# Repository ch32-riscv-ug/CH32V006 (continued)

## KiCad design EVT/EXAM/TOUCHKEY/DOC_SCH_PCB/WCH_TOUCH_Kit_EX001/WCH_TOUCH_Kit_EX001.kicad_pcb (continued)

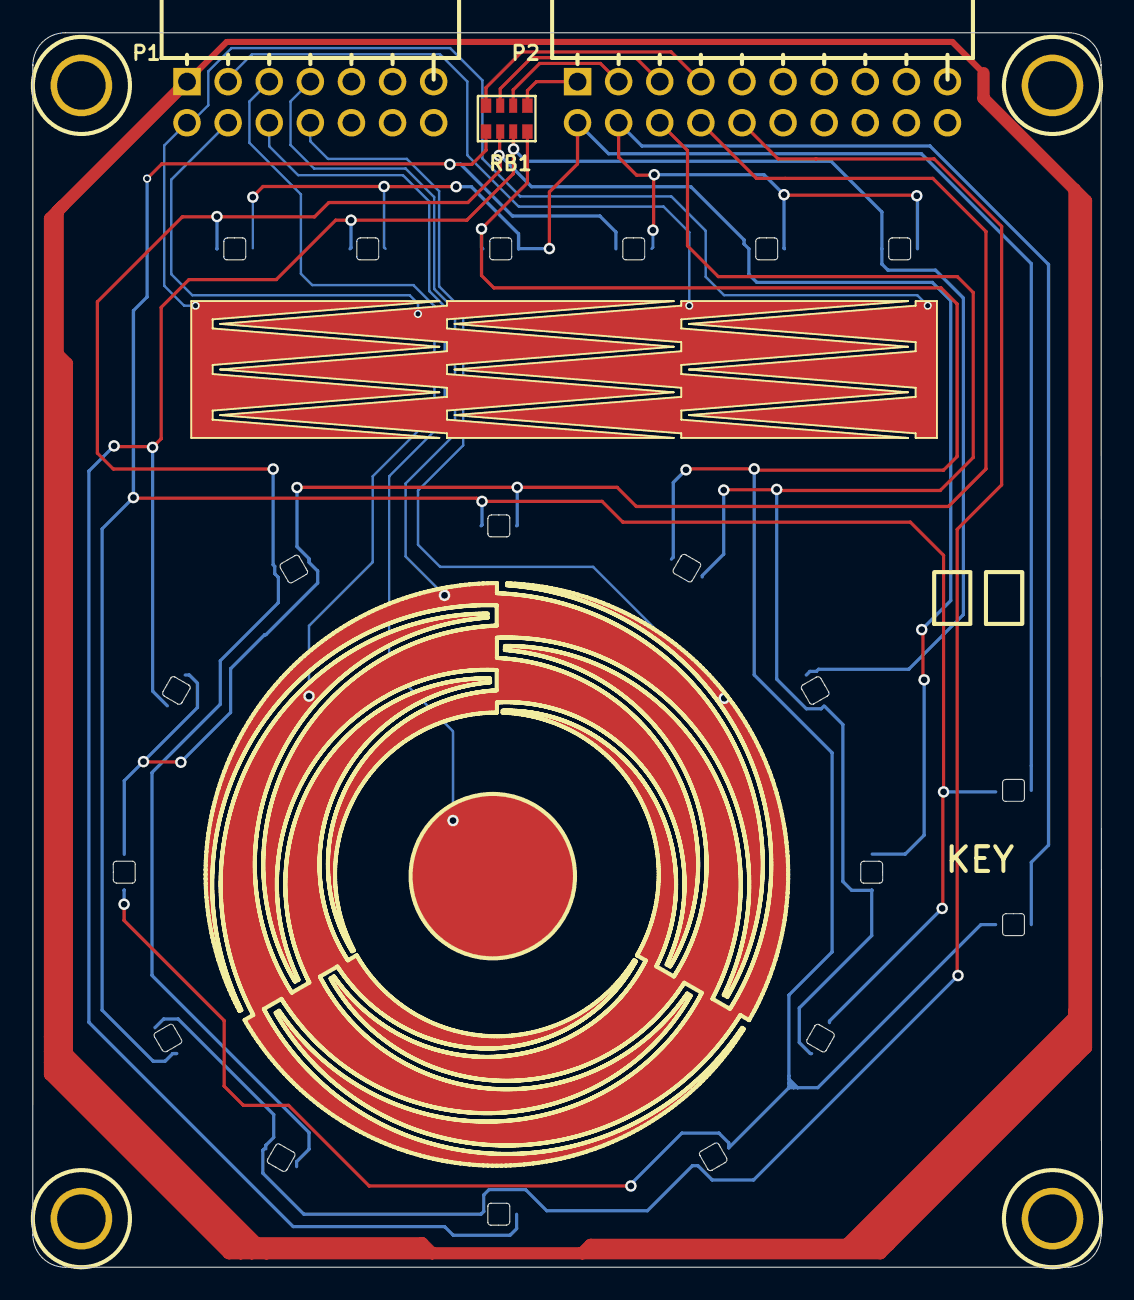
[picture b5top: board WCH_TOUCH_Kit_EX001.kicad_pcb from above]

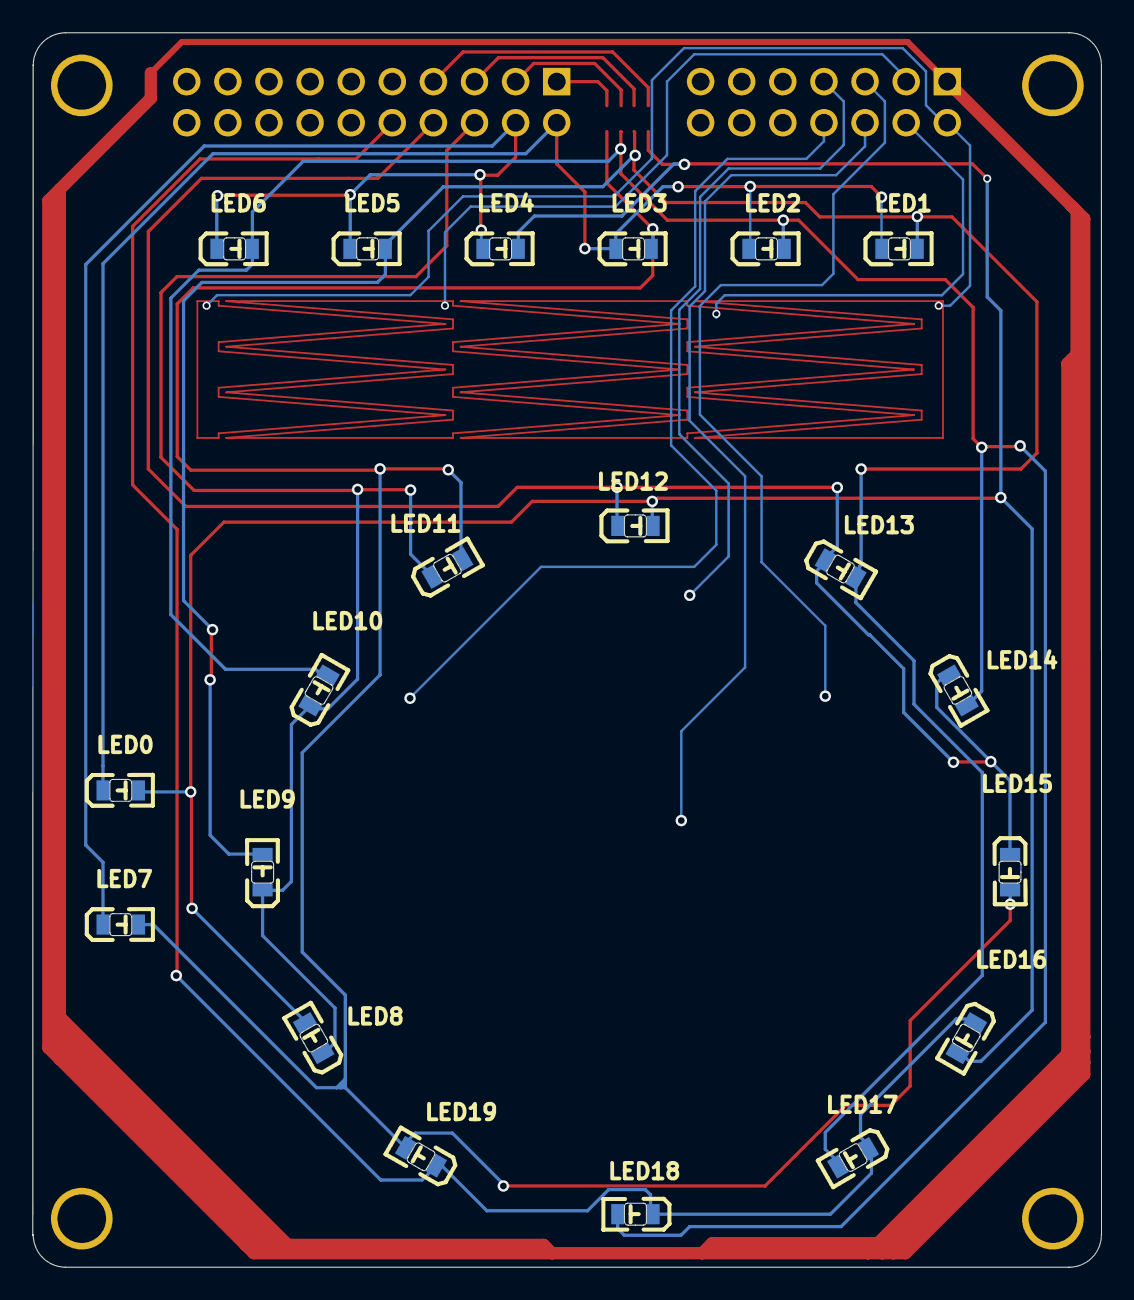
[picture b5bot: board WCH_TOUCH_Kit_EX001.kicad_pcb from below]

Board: 2 copper layers, 66.0 x 76.3 mm, 26 parts (20 on the bottom side), 20 nets.

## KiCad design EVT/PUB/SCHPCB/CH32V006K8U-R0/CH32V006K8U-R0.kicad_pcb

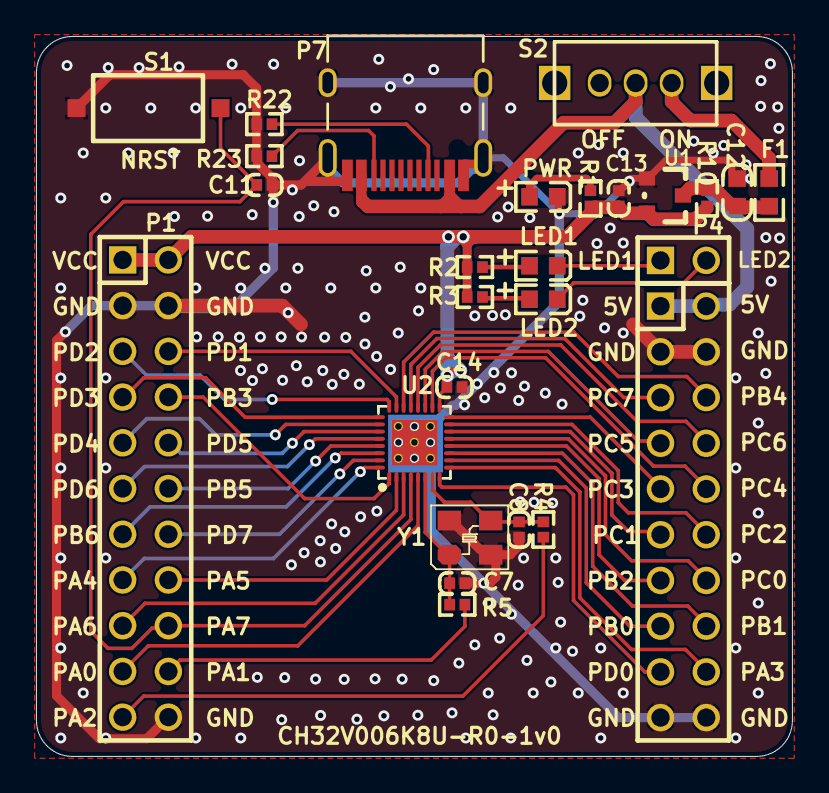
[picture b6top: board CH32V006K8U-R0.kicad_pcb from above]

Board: 2 copper layers, 42.0 x 40.0 mm, 27 parts (0 on the bottom side), 45 nets.

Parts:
C7, C8: 22pF; 0402_C
C11, C14: 0.1uF; 0402_C
C12: 10uF; 0603_C
C13: 2.2uF; 0402_C
F1: 500mA; 0603
LED1: LED1 blue; 0603+
LED2: LED2 blue; 0603+
P1: Header 11X2; IDC22-2.54mm
P2: Header 10X2; IDC20-2.54mm
P4: 2HEAD; SIP2-2.54mm
P7: TYPE-C; TYPE-C-Receptacle-2.0
PWR: POWER red; 0603+
R1, R2, R3: 1K; 0402
R4, R5, R10: 0R; 0402
R22, R23: 5.1K; 0402
S1: NRST; SMD_6.1x3.65x2.5mm-KEY
S2: SW; SW1
U1: 6219P33M; SOT-23
U2: CH32V006K8U; QFN32_4X4
Y1: 24MHz; XT3225

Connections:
+5V: P2.1, P2.2, P7.A4, P7.B4, S2.1
GND: C7.1, C8.1, C11.1, C12.2, C13.1, C14.2, P1.3, P1.4, P1.22, P2.3, P2.4, P2.19, P2.20, P7.0, P7.A1, P7.B1, PWR.2, R22.2, R23.2, S1.2, U1.1, U2.0, Y1.2, Y1.4
LED1: LED1.2, P4.1
LED2: LED2.2, P4.2
NRST: C11.2, P1.18, S1.1, U2.4
NetC12_1: C12.1, F1.2, R10.1, U1.3
NetF1_1: F1.1, S2.3
NetLED1_1: LED1.1, R2.2
NetLED2_1: LED2.1, R3.2
NetP7_A5: P7.A5, R22.1
NetP7_B5: P7.B5, R23.1
NetPWR_1: PWR.1, R1.1
PA0: P1.19, U2.5
PA1: P1.20, R5.2
PA2: P1.21, R4.2
PA3: P2.18, U2.9
PA4: P1.15, U2.32
PA5: P1.16, U2.2
PA6: P1.17, U2.3
PB0: P2.15, U2.10
PB1: P2.16, U2.11
PB2: P2.13, U2.12
PB3: P1.8, U2.1
PB4: P2.6, U2.22
PB5: P1.12, U2.29
PB6: P1.13, U2.30
PC0: P2.14, U2.13
PC1: P2.11, U2.14
PC2: P2.12, U2.15
PC3: P2.9, U2.16
PC4: P2.10, U2.18
PC5: P2.7, U2.19
PC6: P2.8, U2.20
PC7: P2.5, U2.21
PD0: P2.17, U2.8
PD1: P1.6, U2.23
PD2: P1.5, U2.24
PD3: P1.7, U2.25
PD4: P1.9, U2.26
PD5: P1.10, U2.27
PD6: P1.11, U2.28
PD7: P1.14, U2.31
VCC: C13.2, C14.1, P1.1, P1.2, R1.2, R2.1, R3.1, R10.2, U1.2, U2.17
XI: C7.2, R5.1, U2.6, Y1.1
XO: C8.2, R4.1, U2.7, Y1.3

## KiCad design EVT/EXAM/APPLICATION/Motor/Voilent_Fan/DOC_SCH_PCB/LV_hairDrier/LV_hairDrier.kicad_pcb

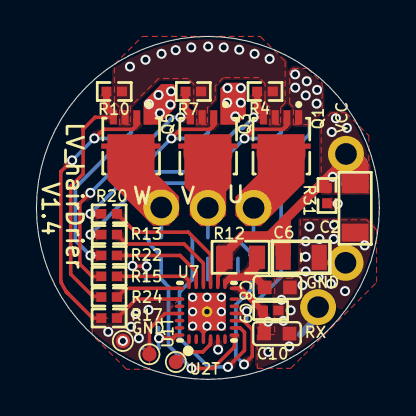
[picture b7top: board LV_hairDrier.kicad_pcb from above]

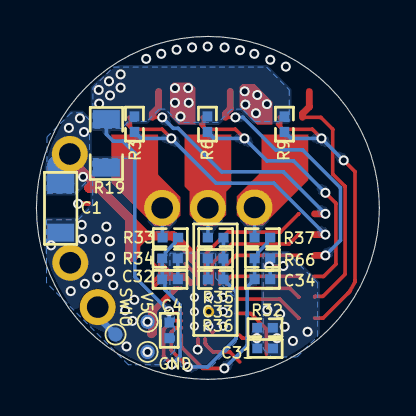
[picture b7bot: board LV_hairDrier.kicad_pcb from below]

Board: 4 copper layers, 19.1 x 19.1 mm, 49 parts (20 on the bottom side), 27 nets.

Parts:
C1, C2: 47uF/25V; M_C1206-
C4: NC(100pF); M_C0402-
C6: 10uF/25V; M_C0805-
C8: 2.2uF/25V; M_C0603
C9, C31: 0.1uF; M_C0402-
C10: 10uF; M_C0603
C32, C33, C34: 1nF; M_C0402-
P1: RX; 2
P11: VCC; 2
P12: GND; 2
P13: W; 2
P14: V; 2
P15: U; 2
Q1, Q3, Q5: M_DFN-8_L3.3_W3.2_2
R3, R6, R9: 20k; M_R0402-
R4, R7, R10: NC(20k); M_R0402-
R12: 100 Ω; M_R0805-
R13, R15, R17, R20, R22, R24: 47Ω; M_R0402-
R19: 0R005/1W; M_R1206-
R31, R33, R35, R37: 5.1k 1%; M_R0402-
R32, R34, R36, R66: 2k 1%; M_R0402-
TP1: U2T; TEST-0.8
TP2: U1T; TEST-0.8
TP3: SWIO; TEST-0.8
TP4, TP6: GND; TEST-0.8
TP5: V5; TEST-0.8
U7: CH32M007E8U; QFN26C_3X3

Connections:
ADC_Vbus: C31.1, R31.1, R32.2, U7.26
BEMF_U: C32.1, R33.1, R34.1, U7.9
BEMF_V: C33.1, R35.1, R36.1, U7.8
BEMF_W: C34.1, R37.1, R66.1, U7.7
GND: C1.1, C2.1, C4.1, C6.2, C8.2, C9.2, C10.2, C31.2, C32.2, C33.2, C34.2, P12.1, R19.1, R32.1, R34.2, R36.2, R66.2, TP4.1, TP6.1, U7.0, U7.3
I1_shunt: C4.2, Q1.1, Q3.1, Q5.1, R3.2, R6.2, R9.2, R19.2, U7.10
M1_CH1_H: R20.1, U7.16
M1_CH1_L: R13.1, U7.17
M1_CH2_H: R22.1, U7.18
M1_CH2_L: R15.1, U7.19
M1_CH3_H: R24.1, U7.20
M1_CH3_L: R17.1, U7.21
M1_U: P15.1, Q1.5, Q1.6, Q1.7, Q1.8, Q1.9, Q1.10, R33.2
M1_V: P14.1, Q3.5, Q3.6, Q3.7, Q3.8, Q3.9, Q3.10, R35.2
M1_W: P13.1, Q5.5, Q5.6, Q5.7, Q5.8, Q5.9, Q5.10, R37.2
NetC8_1: C8.1, R12.1, U7.14
NetQ1_2: Q1.2, R3.1, R13.2
NetQ1_4: Q1.4, R4.2, R20.2
NetQ3_2: Q3.2, R6.1, R15.2
NetQ3_4: Q3.4, R7.1, R22.2
NetQ5_2: Q5.2, R9.1, R17.2
NetQ5_4: Q5.4, R10.1, R24.2
SWIO: P1.1, TP3.1, U7.5
U1_TX: TP2.1, U7.23
U2_TX: TP1.1, U7.4
V5: C9.1, C10.1, TP5.1, U7.13
Vbus: C1.2, C2.2, C6.1, P11.1, Q1.3, Q3.3, Q5.3, R4.1, R7.2, R10.2, R12.2, R31.2, U7.15

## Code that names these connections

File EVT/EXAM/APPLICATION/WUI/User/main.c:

/********************************** (C) COPYRIGHT *******************************
 * File Name          : main.c
 * Author             : WCH
 * Version            : V1.0.0
 * Date               : 2026/08/27
 * Description        : Main program body.
 *********************************************************************************
 * Copyright (c) 2021 Nanjing Qinheng Microelectronics Co., Ltd.
 * Attention: This software (modified or not) and binary are used for 
 * microcontroller manufactured by Nanjing Qinheng Microelectronics.
 *******************************************************************************/

/*
 *@Note
 A demo for wui
  pins: 
    FLASH_CS   -- PC4
    FLASH_DO   -- PC7
    FLASH_DI   -- PC6
    FLASH_CLK  -- PC5
    
    LCD_LED    -- PC0
    LCD_DC     -- PC2
    LCD_RST    -- PC3
    LCD_CS     -- PC1
    LCD_SCK    -- PC5
    LCD_MOSI   -- PC6


 */

#include "debug.h"
#include "string.h"
#include "lcd.h"
#include "wui.h"
#include "wui_user/wui_page.h"
#include "wui_port.h"

#define TIM_PCK (1000ul)
/*********************************************************************
 * @fn      TIM2_init
 *
 * @brief   Initialize TIM2 for WCHGUI
 *        
 * @return  none.
 */
void TIM2_init()
{
    RCC_PB1PeriphClockCmd(RCC_PB1Periph_TIM2, ENABLE);

    TIM_TimeBaseInitTypeDef TIM_TimeBaseInitStructure = {0};

    TIM_Cmd(TIM2, DISABLE);

    TIM_TimeBaseInitStructure.TIM_Period        = 0xffff;
    TIM_TimeBaseInitStructure.TIM_Prescaler     = ((SystemCoreClock) / TIM_PCK) - 1;
    TIM_TimeBaseInitStructure.TIM_ClockDivision = TIM_CKD_DIV1;
    TIM_TimeBaseInitStructure.TIM_CounterMode   = TIM_CounterMode_Up;
    TIM_TimeBaseInit(TIM2, &TIM_TimeBaseInitStructure);

    TIM_ARRPreloadConfig(TIM2, DISABLE);
    TIM_ClearFlag(TIM2, TIM_FLAG_Update);

    TIM_Cmd(TIM2, ENABLE);
}
/*********************************************************************
 * @fn      TIM1_Encoder_Init
 *
 * @brief   Initialize TIM1 for encoder
 *        
 * @return  none.
 */
void TIM1_Encoder_Init()
{
    TIM_TimeBaseInitTypeDef TIM_TimeBaseStructure = {0};
    TIM_ICInitTypeDef       TIM_ICInitStructure = {0};
    GPIO_InitTypeDef        GPIO_InitStructure = {0};

    RCC_PB2PeriphClockCmd(RCC_PB2Periph_GPIOA, ENABLE);
    RCC_PB2PeriphClockCmd(RCC_PB2Periph_TIM1, ENABLE);
    RCC_PB2PeriphClockCmd(RCC_PB2Periph_AFIO, ENABLE);
    RCC_PB2PeriphClockCmd(RCC_PB2Periph_GPIOB, ENABLE);


    GPIO_PinRemapConfig(GPIO_PartialRemap4_TIM1, ENABLE);

    GPIO_InitStructure.GPIO_Pin  = GPIO_Pin_3;
    GPIO_InitStructure.GPIO_Mode = GPIO_Mode_IN_FLOATING;
    GPIO_Init(GPIOA, &GPIO_InitStructure);

    GPIO_InitStructure.GPIO_Pin  = GPIO_Pin_0;
    GPIO_InitStructure.GPIO_Mode = GPIO_Mode_IN_FLOATING;
    GPIO_Init(GPIOB, &GPIO_InitStructure);


    TIM_TimeBaseStructInit(&TIM_TimeBaseStructure);
    TIM_TimeBaseStructure.TIM_Prescaler     = 0x0;
    TIM_TimeBaseStructure.TIM_Period        = 160;
    TIM_TimeBaseStructure.TIM_ClockDivision = TIM_CKD_DIV1;
    TIM_TimeBaseStructure.TIM_CounterMode   = TIM_CounterMode_Up;
    TIM_TimeBaseInit(TIM1, &TIM_TimeBaseStructure);

    TIM_EncoderInterfaceConfig(TIM1, TIM_EncoderMode_TI12, TIM_ICPolarity_Rising, TIM_ICPolarity_Rising);

    TIM_ICStructInit(&TIM_ICInitStructure);
    TIM_ICInitStructure.TIM_ICFilter = 10;
    TIM_ICInit(TIM1, &TIM_ICInitStructure);

    TIM_SetCounter(TIM1, 0);
    TIM_Cmd(TIM1, ENABLE);
}
/*********************************************************************
 * @fn      check_direction
 *
 * @brief    Compute the absolute value of a signed 32-bit integer.
 *        
 * @param   a Signed 32-bit integer.
 *
 * @return  Absolute value of a 
 */
uint32_t static inline iabs(int32_t a)
{
    if (a < 0)
    {
        return -a;
    }
    return a;
}
/*********************************************************************
 * @fn      check_direction
 *
 * @brief   Detect the rotation direction of the encoder
 *        
 * @param   current_value The current count value
 *
 * @return  direction The direction of the encoder's rotation
 */
int32_t check_direction(int current_value)
{

    static int last_value = 0;

    if (current_value == last_value)
    {
        return 0;
    }

    int diff = current_value - last_value;
    if (iabs(diff) < 4)
    {
        return 0;
    }

    int32_t direction;

    if (iabs(diff) < 80)
    {
        if (diff > 0)
        {
            direction = 1;
        }
        else
        {
            direction = -1;
        }
    }
    else
    {
        if (diff > 0)
        {
            direction = -1;
        }
        else
        {
            direction = 1;
        }
    }

    last_value = current_value;
    return direction;
}

#define ENC_KEY_PORT GPIOD
#define ENC_KEY_PIN  (GPIO_Pin_4)

#define ENC_KEY()    ((ENC_KEY_PORT->INDR & ENC_KEY_PIN) == 0)


uint32_t key3_state = 0;
/*********************************************************************
 * @fn      Key_GPIOInit
 *
 * @brief   Initialization of the key pins of the encoder
 *        
 * @return  none.
 */
void Key_GPIOInit(void)
{

    GPIO_InitTypeDef GPIO_InitStructure = {0};

    GPIO_InitStructure.GPIO_Pin  = ENC_KEY_PIN;
    GPIO_InitStructure.GPIO_Mode = GPIO_Mode_IPU;
    GPIO_Init(ENC_KEY_PORT, &GPIO_InitStructure);
}

static uint8_t wui_heap_buffer[2 * 1024];

/*********************************************************************
 * @fn      main
 *
 * @brief   Main program.
 *
 * @return  none
 */
int main(void)
{

    SystemCoreClockUpdate();
    Delay_Init();
#if (SDI_PRINT == SDI_PR_OPEN)
    SDI_Printf_Enable();
#else
    USART_Printf_Init(115200);

#endif
    printf("SystemClk:%d\r\n", SystemCoreClock);
    printf("ChipID:%08x\r\n", DBGMCU_GetCHIPID());

    LCD_Init();
    SPI_FLASH_Init();

    uint32_t id = SPI_Flash_ReadID();
    printf("read id %x\n", id);

    TIM1_Encoder_Init();
    TIM2_init();


    wui_init_data_t init_data = {
        .page_count = WUI_PAGE_COUNT,
        .width      = LCD_WIDTH,
        .height     = LCD_HEIGHT,
        .heap_addr  = wui_heap_buffer,
        .heap_size  = sizeof(wui_heap_buffer),
    };

    wui_init(&init_data);

    wui_register_hal(wui_get_hal());
    wui_page_switch(WUI_START_PAGE);


    while (1)
    {

        uint16_t now = TIM2->CNT;

        if (now > 2)
        {
            TIM2->CNT = 0;

            wui_page_ui_tick(now);
        }
        wui_page_ui_update();

        uint32_t tcnt = TIM1->CNT;

        int32_t dir = check_direction(tcnt);

        if (dir > 0)
        {
            HW_Key_event('a');
        }
        else if (dir < 0)
        {
            HW_Key_event('d');
        }

        uint32_t k3 = ENC_KEY();
        if (k3)
        {
            if (key3_state)
            {
            }
            else
            {
                key3_state = 1;
                HW_Key_event('b');
            }
        }
        else
        {
            key3_state = 0;
        }
    }

    while (1)
        ;
}

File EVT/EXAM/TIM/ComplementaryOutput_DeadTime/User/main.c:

/********************************** (C) COPYRIGHT *******************************
 * File Name          : main.c
 * Author             : WCH
 * Version            : V1.0.0
 * Date               : 2024/01/01
 * Description        : Main program body.
 *********************************************************************************
 * Copyright (c) 2021 Nanjing Qinheng Microelectronics Co., Ltd.
 * Attention: This software (modified or not) and binary are used for 
 * microcontroller manufactured by Nanjing Qinheng Microelectronics.
 *******************************************************************************/

/*
 *@Note
 *complementary output and deadband insertion mode routines:
 *TIM1_CH1(PD2),TIM1_CH1N(PD0)
 *TIM2_CH1(PD4),TIM2_CH1N(PC0),TIM2_CH2(PD3),TIM2_CH2N(PD7),
 *This example demonstrates three complementary output modes with dead zone of TIM1/TIM2: complementary
 *output with dead zone insertion, dead zone waveform delay Greater than the negative pulse, the dead
 *zone waveform delay is greater than the positive pulse.
 *Note:The dead time base of TIM2 is the TIM2 module clock
 *
 */

#include "debug.h"

/* PWM Output Mode Definition */
#define PWM_TIM1   0
#define PWM_TIM2   1

/* PWM Output Mode Selection */
#define PWM_MODE PWM_TIM1
//#define PWM_MODE PWM_TIM2

/*********************************************************************
 * @fn      TIM1_Dead_Time_Init
 *
 * @brief   Initializes TIM1 complementary output and dead time.
 *
 * @param   arr - the period value.
 *          psc - the prescaler value.
 *          ccp - the pulse value.
 *
 * @return  none
 */
void TIM1_Dead_Time_Init(u16 arr, u16 psc, u16 ccp)
{
    GPIO_InitTypeDef        GPIO_InitStructure = {0};
    TIM_OCInitTypeDef       TIM_OCInitStructure = {0};
    TIM_TimeBaseInitTypeDef TIM_TimeBaseInitStructure = {0};
    TIM_BDTRInitTypeDef     TIM_BDTRInitStructure = {0};

    RCC_PB2PeriphClockCmd(RCC_PB2Periph_GPIOD | RCC_PB2Periph_TIM1, ENABLE);

    /* TIM1_CH1 */
    GPIO_InitStructure.GPIO_Pin = GPIO_Pin_2;
    GPIO_InitStructure.GPIO_Mode = GPIO_Mode_AF_PP;
    GPIO_InitStructure.GPIO_Speed = GPIO_Speed_30MHz;
    GPIO_Init(GPIOD, &GPIO_InitStructure);

    /* TIM1_CH1N */
    GPIO_InitStructure.GPIO_Pin = GPIO_Pin_0;
    GPIO_InitStructure.GPIO_Mode = GPIO_Mode_AF_PP;
    GPIO_InitStructure.GPIO_Speed = GPIO_Speed_30MHz;
    GPIO_Init(GPIOD, &GPIO_InitStructure);

    TIM_TimeBaseInitStructure.TIM_Period = arr;
    TIM_TimeBaseInitStructure.TIM_Prescaler = psc;
    TIM_TimeBaseInitStructure.TIM_ClockDivision = TIM_CKD_DIV1;
    TIM_TimeBaseInitStructure.TIM_CounterMode = TIM_CounterMode_Up;
    TIM_TimeBaseInit(TIM1, &TIM_TimeBaseInitStructure);

    TIM_OCInitStructure.TIM_OCMode = TIM_OCMode_PWM2;
    TIM_OCInitStructure.TIM_OutputState = TIM_OutputState_Enable;
    TIM_OCInitStructure.TIM_OutputNState = TIM_OutputNState_Enable;
    TIM_OCInitStructure.TIM_Pulse = ccp;
    TIM_OCInitStructure.TIM_OCPolarity = TIM_OCPolarity_Low;
    TIM_OCInitStructure.TIM_OCNPolarity = TIM_OCNPolarity_Low;
    TIM_OCInitStructure.TIM_OCIdleState = TIM_OCIdleState_Set;
    TIM_OCInitStructure.TIM_OCNIdleState = TIM_OCNIdleState_Reset;
    TIM_OC1Init(TIM1, &TIM_OCInitStructure);

    TIM_BDTRInitStructure.TIM_OSSIState = TIM_OSSIState_Disable;
    TIM_BDTRInitStructure.TIM_OSSRState = TIM_OSSRState_Disable;
    TIM_BDTRInitStructure.TIM_LOCKLevel = TIM_LOCKLevel_OFF;
    TIM_BDTRInitStructure.TIM_DeadTime = 0xFF;
    TIM_BDTRInitStructure.TIM_Break = TIM_Break_Disable;
    TIM_BDTRInitStructure.TIM_BreakPolarity = TIM_BreakPolarity_High;
    TIM_BDTRInitStructure.TIM_AutomaticOutput = TIM_AutomaticOutput_Enable;
    TIM_BDTRConfig(TIM1, &TIM_BDTRInitStructure);

    TIM_CtrlPWMOutputs(TIM1, ENABLE);
    TIM_OC1PreloadConfig(TIM1, TIM_OCPreload_Disable);
    TIM_ARRPreloadConfig(TIM1, ENABLE);
    TIM_Cmd(TIM1, ENABLE);
}

/*********************************************************************
 * @fn      TIM2_Dead_Time_Init
 *
 * @brief   Initializes TIM2 complementary output .
 *
 * @param   arr - the period value.
 *          psc - the prescaler value.
 *          ccp - the pulse value.
 *
 * @return  none
 */
void TIM2_Dead_Time_Init(u16 arr, u16 psc, u16 ccp)
{
    GPIO_InitTypeDef GPIO_InitStructure={0};
    TIM_OCInitTypeDef TIM_OCInitStructure={0};
    TIM_TimeBaseInitTypeDef TIM_TimeBaseInitStructure={0};

    RCC_PB2PeriphClockCmd( RCC_PB2Periph_GPIOC | RCC_PB2Periph_GPIOD, ENABLE );
    RCC_PB1PeriphClockCmd( RCC_PB1Periph_TIM2 ,ENABLE );

    GPIO_InitStructure.GPIO_Pin = GPIO_Pin_4;//CH1
    GPIO_InitStructure.GPIO_Mode = GPIO_Mode_AF_PP;
    GPIO_InitStructure.GPIO_Speed = GPIO_Speed_30MHz;
    GPIO_Init( GPIOD, &GPIO_InitStructure );

    GPIO_InitStructure.GPIO_Pin = GPIO_Pin_3;//CH2
    GPIO_InitStructure.GPIO_Mode = GPIO_Mode_AF_PP;
    GPIO_InitStructure.GPIO_Speed = GPIO_Speed_30MHz;
    GPIO_Init( GPIOD, &GPIO_InitStructure );

    GPIO_InitStructure.GPIO_Pin = GPIO_Pin_0;//CH3
    GPIO_InitStructure.GPIO_Mode = GPIO_Mode_AF_PP;
    GPIO_InitStructure.GPIO_Speed = GPIO_Speed_30MHz;
    GPIO_Init( GPIOC, &GPIO_InitStructure );

    GPIO_InitStructure.GPIO_Pin = GPIO_Pin_7;//CH4
    GPIO_InitStructure.GPIO_Mode = GPIO_Mode_AF_PP;
    GPIO_InitStructure.GPIO_Speed = GPIO_Speed_30MHz;
    GPIO_Init( GPIOD, &GPIO_InitStructure );

    TIM_TimeBaseInitStructure.TIM_Period = arr;
    TIM_TimeBaseInitStructure.TIM_Prescaler = psc;
    TIM_TimeBaseInitStructure.TIM_ClockDivision = TIM_CKD_DIV1;
    TIM_TimeBaseInitStructure.TIM_CounterMode = TIM_CounterMode_Up;

    TIM_TimeBaseInit( TIM2, &TIM_TimeBaseInitStructure);

    TIM_OCInitStructure.TIM_OCMode = TIM_OCMode_PWM1;
    TIM_OCInitStructure.TIM_OutputState = TIM_OutputState_Enable;
    TIM_OCInitStructure.TIM_OutputNState=TIM_OutputNState_Enable;
    TIM_OCInitStructure.TIM_Pulse = ccp;
    TIM_OCInitStructure.TIM_OCPolarity = TIM_OCPolarity_Low;
    TIM_OCInitStructure.TIM_OCNPolarity = TIM_OCNPolarity_High;
    TIM_OCInitStructure.TIM_OCIdleState = TIM_OCIdleState_Set;
    TIM_OCInitStructure.TIM_OCNIdleState = TIM_OCNIdleState_Reset;
    TIM_OC1Init( TIM2, &TIM_OCInitStructure );
    TIM_OC2Init( TIM2, &TIM_OCInitStructure );
    TIM_OC3Init( TIM2, &TIM_OCInitStructure );
    TIM_OC4Init( TIM2, &TIM_OCInitStructure );

    TIM_DeadTimeConfig(TIM2, TIM_Channel_1, 0xF);// TIM_Channel_1 dead time
    TIM_DeadTimeConfig(TIM2, TIM_Channel_2, 0xF); //TIM_Channel_2 dead time

    TIM_CtrlPWMOutputs(TIM2, ENABLE );
    TIM_ARRPreloadConfig( TIM2, ENABLE );
    TIM_Cmd( TIM2, ENABLE );

}

/*********************************************************************
 * @fn      main
 *
 * @brief   Main program.
 *
 * @return  none
 */
int main(void)
{
    SystemCoreClockUpdate();
    Delay_Init();
#if (SDI_PRINT == SDI_PR_OPEN)
    SDI_Printf_Enable();
#else
    USART_Printf_Init(115200);
#endif
    printf("SystemClk:%d\r\n", SystemCoreClock);
    printf( "ChipID:%08x\r\n", DBGMCU_GetCHIPID() );

#if (PWM_MODE==PWM_TIM1)

    /* Complementary output with dead-time insertion */
    TIM1_Dead_Time_Init(100, 48 - 1, 50);
    /* Dead-time waveforms with delay greater than the negative pulse */
    //  TIM1_Dead_Time_Init( 100, 48-1, 10 );
    /* Dead-time waveforms with delay greater than the positive pulse. */
    //  TIM1_Dead_Time_Init( 100, 48-1, 90 );

#elif(PWM_MODE==PWM_TIM2)

    TIM2_Dead_Time_Init(100, 1 - 1, 50);

#endif
    while(1);
}

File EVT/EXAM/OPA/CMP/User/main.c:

/********************************** (C) COPYRIGHT *******************************
 * File Name          : main.c
 * Author             : WCH
 * Version            : V1.0.1
 * Date               : 2026/08/11
 * Description        : Main program body.
 *********************************************************************************
 * Copyright (c) 2021 Nanjing Qinheng Microelectronics Co., Ltd.
 * Attention: This software (modified or not) and binary are used for 
 * microcontroller manufactured by Nanjing Qinheng Microelectronics.
 *******************************************************************************/

/*
 *@Note
 *Comparator routines:
 *CMP1_P0--PC5
 *CMP1_N0--PC2
 *CMP1_OUT--PC0
 *In this example, PC5 and PC2 are postive and negative input, PC0 is the output of the comparator.
 *When the voltage of PC5 is greater than the voltage of PC2, the output of PC0 is high level,
 *otherwise the output of PC0 is low level.
 */

#include "debug.h"
#define OUT_IO      0
#define OUT_TIM     1

//#define CMP_Mode_Out   OUT_IO
#define CMP_Mode_Out   OUT_TIM

/* CMP Reset Enable Definition */
#define CMP_RST_ENABLE   0
#define CMP_RST_DISABLE  1

/* CMP Reset Enable Selection */
#define CMP_RST   CMP_RST_DISABLE
//#define CMP_RST   CMP_RST_ENABLE
/*********************************************************************
 * @fn      CMP_Init
 *
 * @brief   Initializes CMP.
 *
 * @return  none
 */
void CMP_Init( void )
{
    GPIO_InitTypeDef GPIO_InitStructure = {0};
    CMP1_InitTypeDef  CMP_InitStructure = {0};

    RCC_PB2PeriphClockCmd(RCC_PB2Periph_GPIOC, ENABLE);
    GPIO_InitStructure.GPIO_Pin = GPIO_Pin_5|GPIO_Pin_2;
    GPIO_InitStructure.GPIO_Mode = GPIO_Mode_AIN;
    GPIO_Init(GPIOC, &GPIO_InitStructure);

#if  (CMP_Mode_Out == OUT_IO)
    CMP_InitStructure.CMP_Out_Mode = OUT_IO0;
#else
     CMP_InitStructure.CMP_Out_Mode = OUT_IO_TIM1_CH4;
#endif

    CMP_InitStructure.NSEL = CMP_CHN0;
    CMP_InitStructure.PSEL = CMP_CHP0;
    CMP_InitStructure.HYEN = CMP_HYEN_ON;
    OPA_CMP1_Init(&CMP_InitStructure);

#if  (CMP_RST == WDT_RST_ENABLE)
    OPA_CMP_SystemReset_Cmd(CMP1,ENABLE);
#else
    OPA_CMP_SystemReset_Cmd(CMP1,DISABLE);
#endif


    OPA_CMP_FILT_Cmd(ENABLE);
    OPA_CMP_FILT_LEN_Config(CMP_FILT_Len_0);
    OPA_CMP_Cmd(CMP1,ENABLE);
}

/*********************************************************************
 * @fn      CMP_OUT
 *
 * @brief   CMP out program.
 *
 * @return  none
 */
void CMP_OUT( void )
{
    GPIO_InitTypeDef GPIO_InitStructure = {0};

    RCC_PB2PeriphClockCmd( RCC_PB2Periph_GPIOC, ENABLE );
    GPIO_InitStructure.GPIO_Pin = GPIO_Pin_0;
    GPIO_InitStructure.GPIO_Mode = GPIO_Mode_AF_PP;
    GPIO_InitStructure.GPIO_Speed = GPIO_Speed_30MHz;
    GPIO_Init( GPIOC, &GPIO_InitStructure );
}

/*********************************************************************
 * @fn      Input_Capture_Init
 *
 * @brief   Initializes TIM1 input capture.
 *
 * @param   arr - the period value.
 *          psc - the prescaler value.
 *          ccp - the pulse value.
 *
 * @return  none
 */
void Input_Capture_Init(u16 arr, u16 psc)
{

    TIM_ICInitTypeDef       TIM_ICInitStructure = {0};
    TIM_TimeBaseInitTypeDef TIM_TimeBaseInitStructure = {0};
    NVIC_InitTypeDef        NVIC_InitStructure = {0};

    RCC_PB2PeriphClockCmd(RCC_PB2Periph_TIM1, ENABLE);

    TIM_TimeBaseInitStructure.TIM_Period = arr;
    TIM_TimeBaseInitStructure.TIM_Prescaler = psc;
    TIM_TimeBaseInitStructure.TIM_ClockDivision = TIM_CKD_DIV1;
    TIM_TimeBaseInitStructure.TIM_CounterMode = TIM_CounterMode_Up;
    TIM_TimeBaseInitStructure.TIM_RepetitionCounter = 0x00;
    TIM_TimeBaseInit(TIM1, &TIM_TimeBaseInitStructure);

    TIM_ICInitStructure.TIM_Channel = TIM_Channel_4;
    TIM_ICInitStructure.TIM_ICPrescaler = TIM_ICPSC_DIV1;
    TIM_ICInitStructure.TIM_ICFilter = 0x00;
    TIM_ICInitStructure.TIM_ICPolarity = TIM_ICPolarity_Rising;
    TIM_ICInitStructure.TIM_ICSelection = TIM_ICSelection_DirectTI;

    TIM_ICInit(TIM1, &TIM_ICInitStructure);

    NVIC_InitStructure.NVIC_IRQChannel = TIM1_CC_IRQn;
    NVIC_InitStructure.NVIC_IRQChannelPreemptionPriority = 1;
    NVIC_InitStructure.NVIC_IRQChannelSubPriority = 0;
    NVIC_InitStructure.NVIC_IRQChannelCmd = ENABLE;
    NVIC_Init(&NVIC_InitStructure);

    TIM_ITConfig(TIM1, TIM_IT_CC4, ENABLE);
    TIM_Cmd(TIM1, ENABLE);
}

/*********************************************************************
 * @fn      main
 *
 * @brief   Main program.
 *
 * @return  none
 */
int main(void)
{

    SystemCoreClockUpdate();
    Delay_Init();
#if (SDI_PRINT == SDI_PR_OPEN)
    SDI_Printf_Enable();
#else
    USART_Printf_Init( 115200 );
#endif
    printf("SystemClk:%d\r\n", SystemCoreClock);
    printf( "ChipID:%08x\r\n", DBGMCU_GetCHIPID() );
#if  (CMP_RST == WDT_RST_ENABLE)
    printf( "RCC->RSTSCKR:%08x\r\n", RCC->RSTSCKR );
    RCC->RSTSCKR |= (1<<24);
    RCC->RSTSCKR &= ~(1<<24);
#endif

    OPA_CMP_Unlock();
    CMP_Init();
#if  (CMP_Mode_Out == OUT_IO)
       CMP_OUT();
#else
       Input_Capture_Init(0XFFFF,48);
#endif

    while(1);

}
#if  (CMP_Mode_Out == OUT_TIM)

void TIM1_CC_IRQHandler(void) __attribute__((interrupt("WCH-Interrupt-fast")));

/*********************************************************************
 * @fn      TIM1_CC_IRQHandler
 *
 * @brief   This function handles TIM1 Capture Compare Interrupt exception.
 *
 * @return  none
 */
void TIM1_CC_IRQHandler(void)
{
    if( TIM_GetITStatus( TIM1, TIM_IT_CC4 ) != RESET )
    {
        printf( "CH1_Val:%d\r\n", TIM_GetCapture4( TIM1 ) );
        TIM_SetCounter( TIM1, 0 );
    }

    TIM_ClearITPendingBit( TIM1, TIM_IT_CC4 );
}
#endif

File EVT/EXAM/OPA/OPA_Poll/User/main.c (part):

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 *@Note
 *OPA positive input polling function:
 *
 *OPA1_CHN0--PA1
 *OPA1_OUT--PD4
 *P0-PA2 P1-PD7  P2-PD3
 *The number of positive terminals polling is 3. The polling time is 100ms, and the corresponding 
 *channel can be queried when the output is high voltage. OPA can be selected as the brake signal,
 *and the brake is effective when the output is high.
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
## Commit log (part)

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2024-05-15 Rename system.png to system_CH32V006.png
2026-06-15 update update.sh and add GitHub Actions workflow for automated datasheet downloads
2026-06-15 update cron schedule in GitHub Actions workflow and enhance download script with retry logic
2026-06-15 refactor update job to simplify commit logic in GitHub Actions workflow
2026-06-16 update GitHub Actions schedule
2026-06-19 update GitHub Actions workflow to implement keepalive logic and remove unnecessary permissions
2026-06-19 refactor fetch function in update.sh to simplify error handling and remove retry logic
